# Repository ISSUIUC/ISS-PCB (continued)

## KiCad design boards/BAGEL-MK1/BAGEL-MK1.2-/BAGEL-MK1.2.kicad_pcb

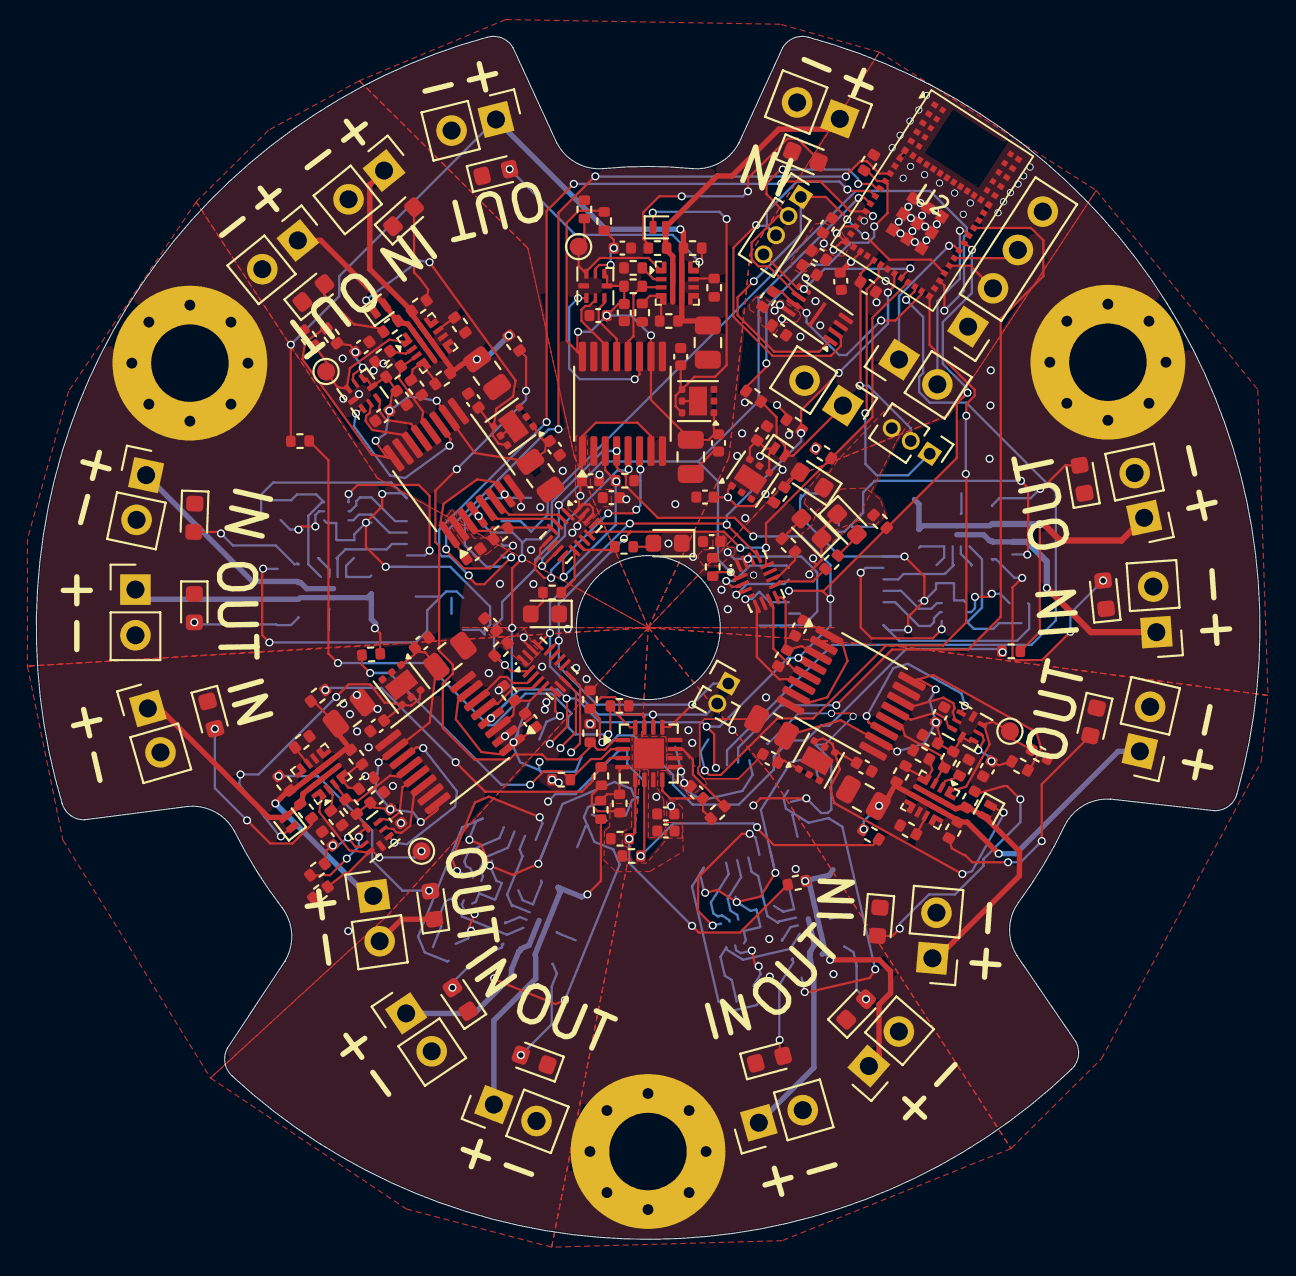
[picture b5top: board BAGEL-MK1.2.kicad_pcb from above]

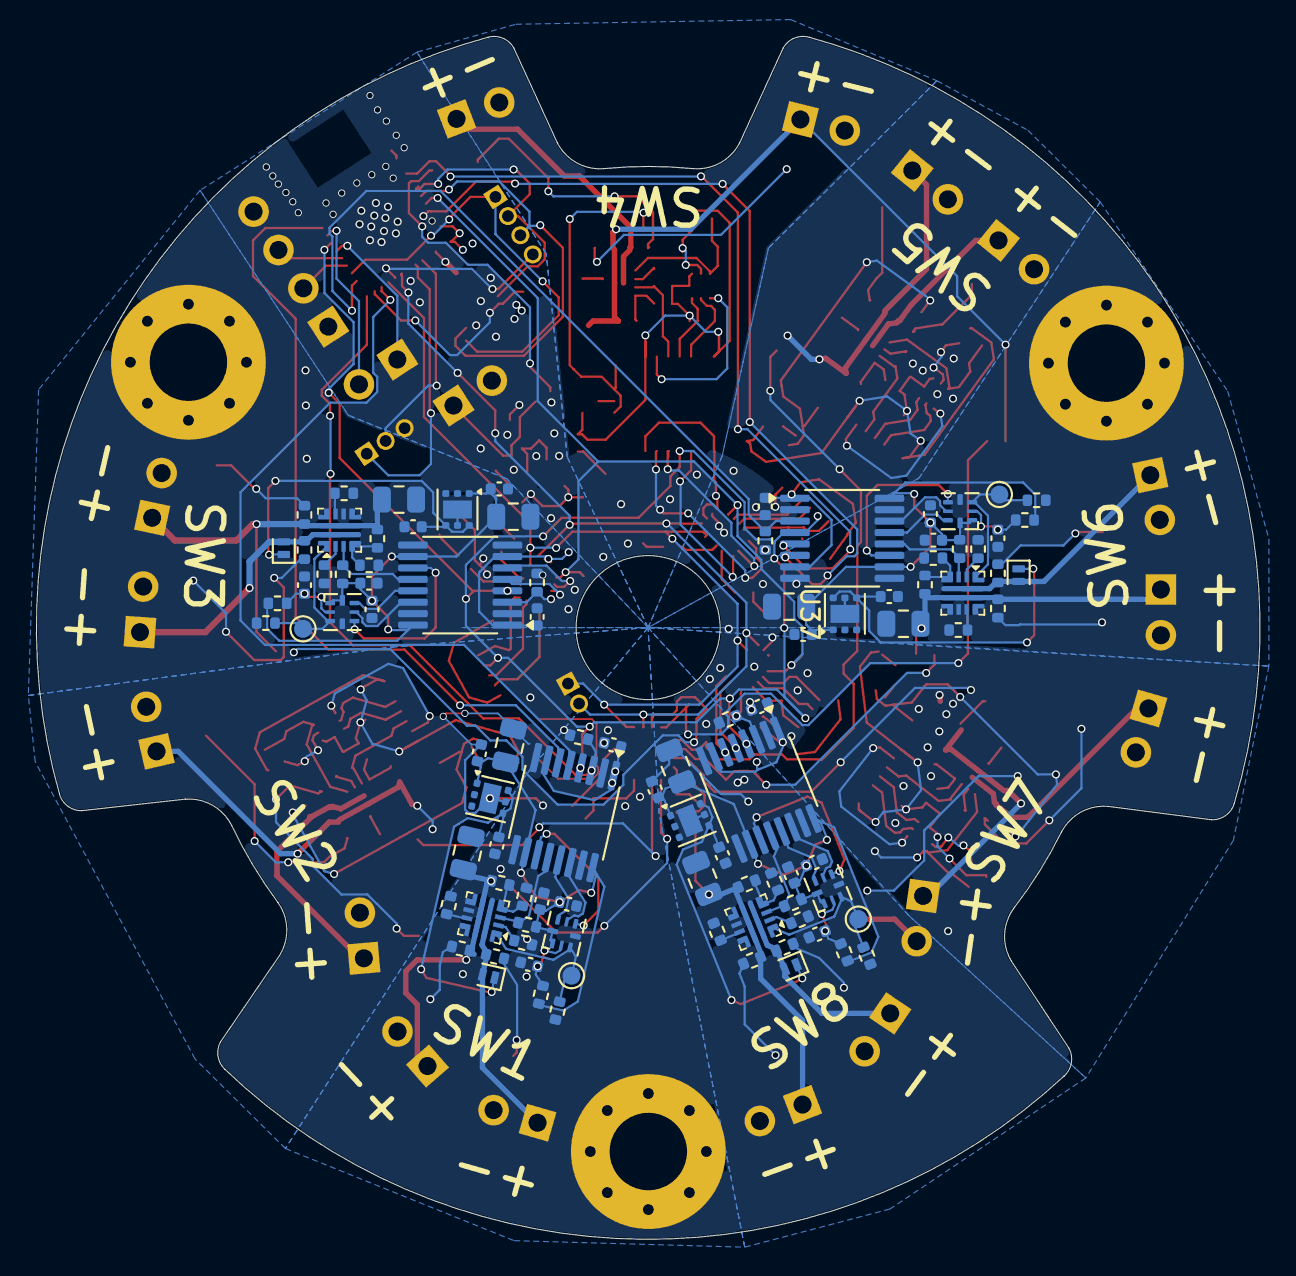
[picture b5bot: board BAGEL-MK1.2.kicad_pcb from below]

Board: 4 copper layers, 68.0 x 66.8 mm, 290 parts (96 on the bottom side), 192 nets.

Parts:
C1, C3, C4, C5, C8, C9, C13, C14, C15, C19, C21, C22, C23, C27, C29, C30, C31, C35, C37, C38, C39, C43, C45, C46, C47, C51, C53, C54, C55, C59, C61, C62, C63, C67, C69, C70, C71, C75, C77: 100nF; C_0402_1005Metric
C2: 4.7uF; C_0402_1005Metric
C6, C10, C11, C12, C16, C24, C32, C40, C48, C56, C64, C72: 1uF; C_0402_1005Metric
C7, C17, C25, C33, C41, C49, C57, C65, C73: 2.2uF; C_0402_1005Metric
C18, C26, C34, C42, C50, C58, C66, C74: 100uF; C_0805_2012Metric
C20, C28, C36, C44, C52, C60, C68, C76: 22uF; C_0805_2012Metric
D1, D7, D10, D13, D16, D19, D22, D25, D28: SDM05U40CSP-7; D_SOD-882
D2, D3, D8, D11, D14, D17, D20, D23, D26, D29: RED; LED_0603_1608Metric
D4: ORANGE; LED_0603_1608Metric
D5, D9, D12, D15, D18, D21, D24, D27, D30: GREEN; LED_0603_1608Metric
D6: BLUE; LED_0603_1608Metric
H1, H2, H3: MountingHole_Pad; MountingHole_4.3mm_M4_Pad_Via
J1: Conn_01x04; PinHeader_1x04_P2.54mm_Vertical
J2: Conn_01x03; PinHeader_1x03_P1.27mm_Vertical
J3: Conn_01x02; PinHeader_1x02_P1.27mm_Vertical
J4, J6, J7, J8, J9, J10, J11, J12, J13, J14, J15, J16, J17, J18, J19, J20, J21, J22: Conn_01x02; PinHeader_1x02_P2.54mm_Vertical
J5: Conn_01x04; PinHeader_1x04_P1.27mm_Vertical
J23, J24, J25, J26, J27, J28, J29, J30: Conn_01x01; TestPoint_Pad_D1.0mm
R1, R2, R3, R12, R15, R16, R18, R19, R25, R26, R28, R29, R35, R36, R38, R39, R45, R46, R48, R49, R55, R56, R58, R59, R65, R66, R68, R69, R75, R76, R78, R79, R85, R86, R88, R89, R95: 10k; R_0402_1005Metric
R4, R6, R7, R8, R9, R10, R11, R17, R27, R37, R47, R57, R67, R77, R87: 4.7k; R_0402_1005Metric
R5, R13, R14, R96, R97, R98, R99, R100, R101, R102, R103, R104, R105, R106, R107, R108, R109, R110, R111: 100k; R_0402_1005Metric
R20, R30, R40, R50, R60, R70, R80, R90: 680; R_0402_1005Metric
R21, R31, R41, R51, R61, R71, R81, R91: 390k; R_0402_1005Metric
R22, R32, R42, R52, R62, R72, R82, R92: 300k; R_0402_1005Metric
R23, R33, R43, R53, R63, R73, R83, R93: 500k; R_0402_1005Metric
R24, R34, R44, R54, R64, R74, R84, R94: 1k; R_0402_1005Metric
U1: W25Q16JLUX; Winbond_USON-8-1EP_3x2mm_P0.5mm_EP0.2x1.6mm
U2: STM32WB1MMC; ST_LGA-77_6.5x10mm_P0.45-0.5mm
U3, U9, U13, U17, U21, U25, U29, U33, U37: TPS7A25; WSON-6-1EP_2x2mm_P0.65mm_EP1x1.6mm
U4, U5, U39: TCAL9538; UQFN-16_1.8x2.6mm_P0.4mm
U6: ADS7138-Q1; WQFN-16-1EP_3x3mm_P0.5mm_EP1.68x1.68mm
U7, U11, U15, U19, U23, U27, U31, U35: ISO7742; SSOP-16_3.9x4.9mm_P0.635mm
U8, U12, U16, U20, U24, U28, U32, U36: SN74AUP1G74RSER; UQFN-RSE0008A
U10, U14, U18, U22, U26, U30, U34, U38: TPS25947; VQFN-HR-RPW0010A

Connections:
/BLUE_LED: R9.1, U5.10 (P7)
/BOOT: J2.2, R2.2, U2.22 (BOOT0)
/EXP_RESET: R3.1, R95.1, U2.13 (PA2), U4.1 (~RESET), U5.1 (~RESET), U39.1 (~RESET)
/FLASH_CS: J5.1, U1.1 (~CS), U2.33 (PB4)
/FLASH_RESET: R1.2, U1.7 (~HOLD/~RESET/IO_{3}), U2.29 (PA7)
/GPIO_Clock: R12.2, U2.37 (PA0), U7.4 (INB), U11.4 (INB), U15.4 (INB), U19.4 (INB), U23.4 (INB), U27.4 (INB), U31.4 (INB), U35.4 (INB)
/GREEN_LED: R8.1, U5.9 (P6)
/I2C_SCL: J3.1, R11.1, U2.27 (PB6), U4.12 (SCL), U5.12 (SCL), U6.13 (SCL), U39.12 (SCL)
/I2C_SDA: J3.2, R10.1, U2.25 (PB7), U4.13 (SDA), U5.13 (SDA), U6.14 (SDA), U39.13 (SDA)
/MainBatt_V: D1.2 (A), J6.1, R13.2
/NRST: J2.1, U2.23 (NRST)
/ORANGE_LED: R7.1, U4.10 (P7)
/PG_ISO_1: U2.28 (PA3), U15.5 (OUTC)
/PG_ISO_2: U4.7 (P4), U19.5 (OUTC)
/PG_ISO_3: U4.3 (P1), U23.5 (OUTC)
/PG_ISO_4: U5.7 (P4), U27.5 (OUTC)
/PG_ISO_5: U5.3 (P1), U31.5 (OUTC)
/PG_ISO_6: U2.9 (PA4), U35.5 (OUTC)
/PG_ISO_7: U7.5 (OUTC), U39.3 (P1)
/PG_ISO_8: U11.5 (OUTC), U39.7 (P4)
/RED_LED: R6.1, U4.9 (P6)
/SPI_MISO: J5.3, U1.2 (DO/IO_{1}), U2.12 (PA6)
/SPI_MOSI: J5.4, U1.5 (DI/IO_{0}), U2.26 (PB5)
/SPI_SCK: J5.2, U1.6 (CLK), U2.11 (PA1)
/SWCLK: J1.2, U2.34 (PA14)
/SWDIO: J1.3, U2.35 (PA13)
/SubBatt_GND1: C29.2, C31.2, C32.2, C33.2, C34.2, C35.1, C36.2, D14.1 (K), D15.1 (K), J7.2, J8.2, R36.1, R40.1, R41.2, R43.2, U15.9 (GND2), U15.15 (GND2), U16.4 (GND), U17.5 (GND), U17.7 (Thermal), U18.8 (GND)
/SubBatt_GND2: C37.2, C39.2, C40.2, C41.2, C42.2, C43.1, C44.2, D17.1 (K), D18.1 (K), J9.2, J10.2, R46.1, R50.1, R51.2, R53.2, U19.9 (GND2), U19.15 (GND2), U20.4 (GND), U21.5 (GND), U21.7 (Thermal), U22.8 (GND)
/SubBatt_GND3: C45.2, C47.2, C48.2, C49.2, C50.2, C51.1, C52.2, D20.1 (K), D21.1 (K), J11.2, J12.2, R56.1, R60.1, R61.2, R63.2, U23.9 (GND2), U23.15 (GND2), U24.4 (GND), U25.5 (GND), U25.7 (Thermal), U26.8 (GND)
/SubBatt_GND4: C53.2, C55.2, C56.2, C57.2, C58.2, C59.1, C60.2, D23.1 (K), D24.1 (K), J13.2, J14.2, R66.1, R70.1, R71.2, R73.2, U27.9 (GND2), U27.15 (GND2), U28.4 (GND), U29.5 (GND), U29.7 (Thermal), U30.8 (GND)
/SubBatt_GND5: C61.2, C63.2, C64.2, C65.2, C66.2, C67.1, C68.2, D26.1 (K), D27.1 (K), J15.2, J16.2, R76.1, R80.1, R81.2, R83.2, U31.9 (GND2), U31.15 (GND2), U32.4 (GND), U33.5 (GND), U33.7 (Thermal), U34.8 (GND)
/SubBatt_GND6: C69.2, C71.2, C72.2, C73.2, C74.2, C75.1, C76.2, D29.1 (K), D30.1 (K), J17.2, J18.2, R86.1, R90.1, R91.2, R93.2, U35.9 (GND2), U35.15 (GND2), U36.4 (GND), U37.5 (GND), U37.7 (Thermal), U38.8 (GND)
/SubBatt_GND7: C13.2, C15.2, C16.2, C17.2, C18.2, C19.1, C20.2, D8.1 (K), D9.1 (K), J19.2, J20.2, R16.1, R20.1, R21.2, R23.2, U7.9 (GND2), U7.15 (GND2), U8.4 (GND), U9.5 (GND), U9.7 (Thermal), U10.8 (GND)
/SubBatt_GND8: C21.2, C23.2, C24.2, C25.2, C26.2, C27.1, C28.2, D11.1 (K), D12.1 (K), J21.2, J22.2, R26.1, R30.1, R31.2, R33.2, U11.9 (GND2), U11.15 (GND2), U12.4 (GND), U13.5 (GND), U13.7 (Thermal), U14.8 (GND)
/SubBatt_V1: D13.2 (A), J7.1, R37.1, U18.5 (IN)
/SubBatt_V2: D16.2 (A), J9.1, R47.1, U22.5 (IN)
/SubBatt_V3: D19.2 (A), J11.1, R57.1, U26.5 (IN)
/SubBatt_V4: D22.2 (A), J13.1, R67.1, U30.5 (IN)
/SubBatt_V5: D25.2 (A), J15.1, R77.1, U34.5 (IN)
/SubBatt_V6: D28.2 (A), J17.1, R87.1, U38.5 (IN)
/SubBatt_V7: D7.2 (A), J19.1, R17.1, U10.5 (IN)
/SubBatt_V8: D10.2 (A), J21.1, R27.1, U14.5 (IN)
/Switch 1/PG: R39.2, U15.12 (INC), U18.3 (PG/AUXOFF)
/Switch 1/Q: J25.1 (Pin_1_1), R36.2, U16.3 (Q), U18.1 (EN/UVLO)
/Switch 1/Reg_V: C29.1, C31.1, C33.1, C34.1, R38.1, R39.1, U15.10 (EN2), U15.16 (VCC2), U16.1 (~PRE), U16.8 (VCC), U17.1 (VOUT)
/Switch 1/~CLR: C35.2, R38.2, U16.2 (~CLR)
/Switch 1/~Q: U15.11 (IND), U16.5 (~Q)
/Switch 2/PG: R49.2, U19.12 (INC), U22.3 (PG/AUXOFF)
/Switch 2/Q: J26.1 (Pin_1_1), R46.2, U20.3 (Q), U22.1 (EN/UVLO)
/Switch 2/Reg_V: C37.1, C39.1, C41.1, C42.1, R48.1, R49.1, U19.10 (EN2), U19.16 (VCC2), U20.1 (~PRE), U20.8 (VCC), U21.1 (VOUT)
/Switch 2/~CLR: C43.2, R48.2, U20.2 (~CLR)
/Switch 2/~Q: U19.11 (IND), U20.5 (~Q)
/Switch 3/PG: R59.2, U23.12 (INC), U26.3 (PG/AUXOFF)
/Switch 3/Q: J27.1 (Pin_1_1), R56.2, U24.3 (Q), U26.1 (EN/UVLO)
/Switch 3/Reg_V: C45.1, C47.1, C49.1, C50.1, R58.1, R59.1, U23.10 (EN2), U23.16 (VCC2), U24.1 (~PRE), U24.8 (VCC), U25.1 (VOUT)
/Switch 3/~CLR: C51.2, R58.2, U24.2 (~CLR)
/Switch 3/~Q: U23.11 (IND), U24.5 (~Q)
/Switch 4/PG: R69.2, U27.12 (INC), U30.3 (PG/AUXOFF)
/Switch 4/Q: J28.1 (Pin_1_1), R66.2, U28.3 (Q), U30.1 (EN/UVLO)
/Switch 4/Reg_V: C53.1, C55.1, C57.1, C58.1, R68.1, R69.1, U27.10 (EN2), U27.16 (VCC2), U28.1 (~PRE), U28.8 (VCC), U29.1 (VOUT)
/Switch 4/~CLR: C59.2, R68.2, U28.2 (~CLR)
/Switch 4/~Q: U27.11 (IND), U28.5 (~Q)
/Switch 5/PG: R79.2, U31.12 (INC), U34.3 (PG/AUXOFF)
/Switch 5/Q: J29.1 (Pin_1_1), R76.2, U32.3 (Q), U34.1 (EN/UVLO)
/Switch 5/Reg_V: C61.1, C63.1, C65.1, C66.1, R78.1, R79.1, U31.10 (EN2), U31.16 (VCC2), U32.1 (~PRE), U32.8 (VCC), U33.1 (VOUT)
/Switch 5/~CLR: C67.2, R78.2, U32.2 (~CLR)
/Switch 5/~Q: U31.11 (IND), U32.5 (~Q)
/Switch 6/PG: R89.2, U35.12 (INC), U38.3 (PG/AUXOFF)
/Switch 6/Q: J30.1 (Pin_1_1), R86.2, U36.3 (Q), U38.1 (EN/UVLO)
/Switch 6/Reg_V: C69.1, C71.1, C73.1, C74.1, R88.1, R89.1, U35.10 (EN2), U35.16 (VCC2), U36.1 (~PRE), U36.8 (VCC), U37.1 (VOUT)
/Switch 6/~CLR: C75.2, R88.2, U36.2 (~CLR)
/Switch 6/~Q: U35.11 (IND), U36.5 (~Q)
/Switch 7/PG: R19.2, U7.12 (INC), U10.3 (PG/AUXOFF)
/Switch 7/Q: J23.1 (Pin_1_1), R16.2, U8.3 (Q), U10.1 (EN/UVLO)
/Switch 7/Reg_V: C13.1, C15.1, C17.1, C18.1, R18.1, R19.1, U7.10 (EN2), U7.16 (VCC2), U8.1 (~PRE), U8.8 (VCC), U9.1 (VOUT)
/Switch 7/~CLR: C19.2, R18.2, U8.2 (~CLR)
/Switch 7/~Q: U7.11 (IND), U8.5 (~Q)
/Switch 8/PG: R29.2, U11.12 (INC), U14.3 (PG/AUXOFF)
/Switch 8/Q: J24.1 (Pin_1_1), R26.2, U12.3 (Q), U14.1 (EN/UVLO)
/Switch 8/Reg_V: C21.1, C23.1, C25.1, C26.1, R28.1, R29.1, U11.10 (EN2), U11.16 (VCC2), U12.1 (~PRE), U12.8 (VCC), U13.1 (VOUT)
/Switch 8/~CLR: C27.2, R28.2, U12.2 (~CLR)
/Switch 8/~Q: U11.11 (IND), U12.5 (~Q)
/Switch_1: R35.1, U2.30 (PA12), U15.3 (INA)
/Switch_2: R45.1, U4.8 (P5), U19.3 (INA)
/Switch_3: R55.1, U4.4 (P2), U23.3 (INA)
/Switch_4: R65.1, U5.8 (P5), U27.3 (INA)
/Switch_5: R75.1, U5.4 (P2), U31.3 (INA)
/Switch_6: R85.1, U2.32 (PA11), U35.3 (INA)
/Switch_7: R15.1, U7.3 (INA), U39.4 (P2)
/Switch_8: R25.1, U11.3 (INA), U39.5 (P3)
/UART_RX: J4.1, U2.36 (PA10)
/UART_TX: J4.2, U2.38 (PA9)
/VOUT_SENSE_1: R96.1, R97.2, U6.5 (AIN6/GPIO6)
/VOUT_SENSE_2: R98.1, R99.2, U6.6 (AIN7/GPIO7)
/VOUT_SENSE_3: R100.1, R101.2, U6.15 (AIN0/GPIO0)
/VOUT_SENSE_4: R102.1, R103.2, U6.16 (AIN1/GPIO1)
/VOUT_SENSE_5: R104.1, R105.2, U6.1 (ANI2/GPIO2)
/VOUT_SENSE_6: R106.1, R107.2, U6.2 (AIN3/GPIO3)
/VOUT_SENSE_7: R108.1, R109.2, U6.3 (AIN4/GPIO4)
/VOUT_SENSE_8: R110.1, R111.2, U6.4 (AIN5/GPIO5)
/V_SENSE: R13.1, R14.2, U2.10 (PA8)
/V_out_1: C36.1, J8.1, R42.1, R44.1, R96.2, U18.6 (OUT)
/V_out_2: C44.1, J10.1, R52.1, R54.1, R98.2, U22.6 (OUT)
/V_out_3: C52.1, J12.1, R62.1, R64.1, R100.2, U26.6 (OUT)
/V_out_4: C60.1, J14.1, R72.1, R74.1, R102.2, U30.6 (OUT)
/V_out_5: C68.1, J16.1, R82.1, R84.1, R104.2, U34.6 (OUT)
/V_out_6: C76.1, J18.1, R92.1, R94.1, R106.2, U38.6 (OUT)
/V_out_7: C20.1, J20.1, R22.1, R24.1, R108.2, U10.6 (OUT)
/V_out_8: C28.1, J22.1, R32.1, R34.1, R110.2, U14.6 (OUT)
/~Q_ISO_1: U2.39 (PA5), U15.6 (OUTD)
/~Q_ISO_2: U4.5 (P3), U19.6 (OUTD)
/~Q_ISO_3: U4.2 (P0), U23.6 (OUTD)
/~Q_ISO_4: U5.5 (P3), U27.6 (OUTD)
/~Q_ISO_5: U5.2 (P0), U31.6 (OUTD)
/~Q_ISO_6: U2.14 (PB8), U35.6 (OUTD)
/~Q_ISO_7: U7.6 (OUTD), U39.2 (P0)
/~Q_ISO_8: U11.6 (OUTD), U39.8 (P5)
MCU_GND: C1.2, C2.2, C3.2, C4.2, C5.2, C6.2, C7.2, C8.2, C9.2, C11.2, C12.2, C14.2, C22.2, C30.2, C38.2, C46.2, C54.2, C62.2, C70.2, C77.2, D2.1 (K), D3.1 (K), D4.1 (K), D5.1 (K), D6.1 (K), J1.4, J2.3, J6.2, R2.1, R12.1, R14.1, R15.2, R25.2, R35.2, R45.2, R55.2, R65.2, R75.2, R85.2, R97.1, R99.1, R101.1, R103.1, R105.1, R107.1, R109.1, R111.1, U1.4 (GND), U1.9 (EP), U2.1 (VSS), U2.2 (VSS), U2.3 (VSS), U2.4 (VSS), U2.5 (VSSRF), U2.8 (VSSRF), U2.15 (VSS), U2.17 (VSS), U2.19 (VSS), U2.21 (VSSSMPS), U2.24 (VSS), U2.31 (VSS), U2.43 (VSS), U2.44 (VSS), U2.45 (VSS), U2.46 (VSS), U2.47 (VSS), U2.48 (VSS), U2.49 (VSS), U2.50 (VSS), U2.51 (VSS), U2.52 (VSS), U2.53 (VSS), U2.54 (VSS), U2.55 (VSS), U2.56 (VSS), U2.57 (VSS), U2.58 (VSS), U2.59 (VSS), U2.60 (VSS), U2.61 (VSS), U2.62 (VSS), U2.63 (VSS), U2.64 (VSS), U2.65 (VSS), U2.66 (VSS), U2.67 (VSS), U2.68 (VSS), U2.69 (VSS), U2.70 (VSS), U2.71 (VSS), U2.72 (VSS), U2.73 (VSS), U2.74 (VSS), U2.75 (VSS), U2.76 (VSS), U2.77 (VSS), U3.5 (GND), U3.7 (Thermal), U4.6 (GND), U4.16 (A1), U5.6 (GND), U5.15 (A0), U7.2 (GND1), U7.8 (GND1), U11.2 (GND1), U11.8 (GND1), U15.2 (GND1), U15.8 (GND1), U19.2 (GND1), U19.8 (GND1), U23.2 (GND1), U23.8 (GND1), U27.2 (GND1), U27.8 (GND1), U31.2 (GND1), U31.8 (GND1), U35.2 (GND1), U35.8 (GND1), U39.6 (GND)
MCU_V: C1.1, C2.1, C3.1, C4.1, C5.1, C7.1, C8.1, C9.1, C10.2, C11.1, C12.1, C14.1, C22.1, C30.1, C38.1, C46.1, C54.1, C62.1, C70.1, C77.1, J1.1, R1.1, R3.2, R4.2, R10.2, R11.2, R95.2, U1.8 (VCC), U2.16 (VDDA), U2.18 (VBAT), U2.20 (VDDSMPS), U3.1 (VOUT), U4.14 (VCC), U4.15 (A0), U5.14 (VCC), U5.16 (A1), U6.7 (AVDD), U6.9 (GND), U6.10 (DVDD), U6.17 (EPAD), U7.1 (VCC1), U7.7 (EN1), U11.1 (VCC1), U11.7 (EN1), U15.1 (VCC1), U15.7 (EN1), U19.1 (VCC1), U19.7 (EN1), U23.1 (VCC1), U23.7 (EN1), U27.1 (VCC1), U27.7 (EN1), U31.1 (VCC1), U31.7 (EN1), U35.1 (VCC1), U35.7 (EN1), U39.14 (VCC), U39.15 (A0), U39.16 (A1)
unnamed: C6.1, D1.1 (K), U3.4 (EN), U3.6 (VIN)
unnamed: D2.2 (A), R4.1
unnamed: D3.2 (A), R6.2
unnamed: D4.2 (A), R7.2
unnamed: D5.2 (A), R8.2
unnamed: D6.2 (A), R9.2
unnamed: C16.1, D7.1 (K), U9.4 (EN), U9.6 (VIN)
unnamed: D8.2 (A), R17.2
unnamed: D9.2 (A), R24.2
unnamed: C24.1, D10.1 (K), U13.4 (EN), U13.6 (VIN)
unnamed: D11.2 (A), R27.2
unnamed: D12.2 (A), R34.2
unnamed: C32.1, D13.1 (K), U17.4 (EN), U17.6 (VIN)
unnamed: D14.2 (A), R37.2
unnamed: D15.2 (A), R44.2
unnamed: C40.1, D16.1 (K), U21.4 (EN), U21.6 (VIN)
unnamed: D17.2 (A), R47.2
unnamed: D18.2 (A), R54.2
unnamed: C48.1, D19.1 (K), U25.4 (EN), U25.6 (VIN)
unnamed: D20.2 (A), R57.2
unnamed: D21.2 (A), R64.2
unnamed: C56.1, D22.1 (K), U29.4 (EN), U29.6 (VIN)
unnamed: D23.2 (A), R67.2
unnamed: D24.2 (A), R74.2
unnamed: C64.1, D25.1 (K), U33.4 (EN), U33.6 (VIN)
unnamed: D26.2 (A), R77.2
unnamed: D27.2 (A), R84.2
unnamed: C72.1, D28.1 (K), U37.4 (EN), U37.6 (VIN)
unnamed: D29.2 (A), R87.2
unnamed: D30.2 (A), R94.2
unnamed: U2.6 (ANT_IN), U2.7 (ANT_OUT)
unnamed: R5.1, U6.11 (ADDR)
unnamed: C10.1, R5.2, U6.8 (DECAP)
unnamed: U7.14 (OUTA), U8.6 (D)
unnamed: U7.13 (OUTB), U8.7 (CLK)
unnamed: R20.2, U10.9 (ILM)
unnamed: R21.1, U10.2 (OVLO/OVCSEL)
unnamed: R22.2, R23.1, U10.4 (PGTH/NFLT)
unnamed: U11.14 (OUTA), U12.6 (D)
unnamed: U11.13 (OUTB), U12.7 (CLK)
unnamed: R30.2, U14.9 (ILM)
unnamed: R31.1, U14.2 (OVLO/OVCSEL)
unnamed: R32.2, R33.1, U14.4 (PGTH/NFLT)
unnamed: U15.14 (OUTA), U16.6 (D)
unnamed: U15.13 (OUTB), U16.7 (CLK)
unnamed: R40.2, U18.9 (ILM)
unnamed: R41.1, U18.2 (OVLO/OVCSEL)
unnamed: R42.2, R43.1, U18.4 (PGTH/NFLT)
unnamed: U19.14 (OUTA), U20.6 (D)
unnamed: U19.13 (OUTB), U20.7 (CLK)
unnamed: R50.2, U22.9 (ILM)
unnamed: R51.1, U22.2 (OVLO/OVCSEL)
unnamed: R52.2, R53.1, U22.4 (PGTH/NFLT)
unnamed: U23.14 (OUTA), U24.6 (D)
unnamed: U23.13 (OUTB), U24.7 (CLK)
unnamed: R60.2, U26.9 (ILM)
unnamed: R61.1, U26.2 (OVLO/OVCSEL)
unnamed: R62.2, R63.1, U26.4 (PGTH/NFLT)
unnamed: U27.14 (OUTA), U28.6 (D)
unnamed: U27.13 (OUTB), U28.7 (CLK)
unnamed: R70.2, U30.9 (ILM)
unnamed: R71.1, U30.2 (OVLO/OVCSEL)
unnamed: R72.2, R73.1, U30.4 (PGTH/NFLT)
unnamed: U31.14 (OUTA), U32.6 (D)
unnamed: U31.13 (OUTB), U32.7 (CLK)
unnamed: R80.2, U34.9 (ILM)
unnamed: R81.1, U34.2 (OVLO/OVCSEL)
unnamed: R82.2, R83.1, U34.4 (PGTH/NFLT)
unnamed: U35.14 (OUTA), U36.6 (D)
unnamed: U35.13 (OUTB), U36.7 (CLK)
unnamed: R90.2, U38.9 (ILM)
unnamed: R91.1, U38.2 (OVLO/OVCSEL)
unnamed: R92.2, R93.1, U38.4 (PGTH/NFLT)

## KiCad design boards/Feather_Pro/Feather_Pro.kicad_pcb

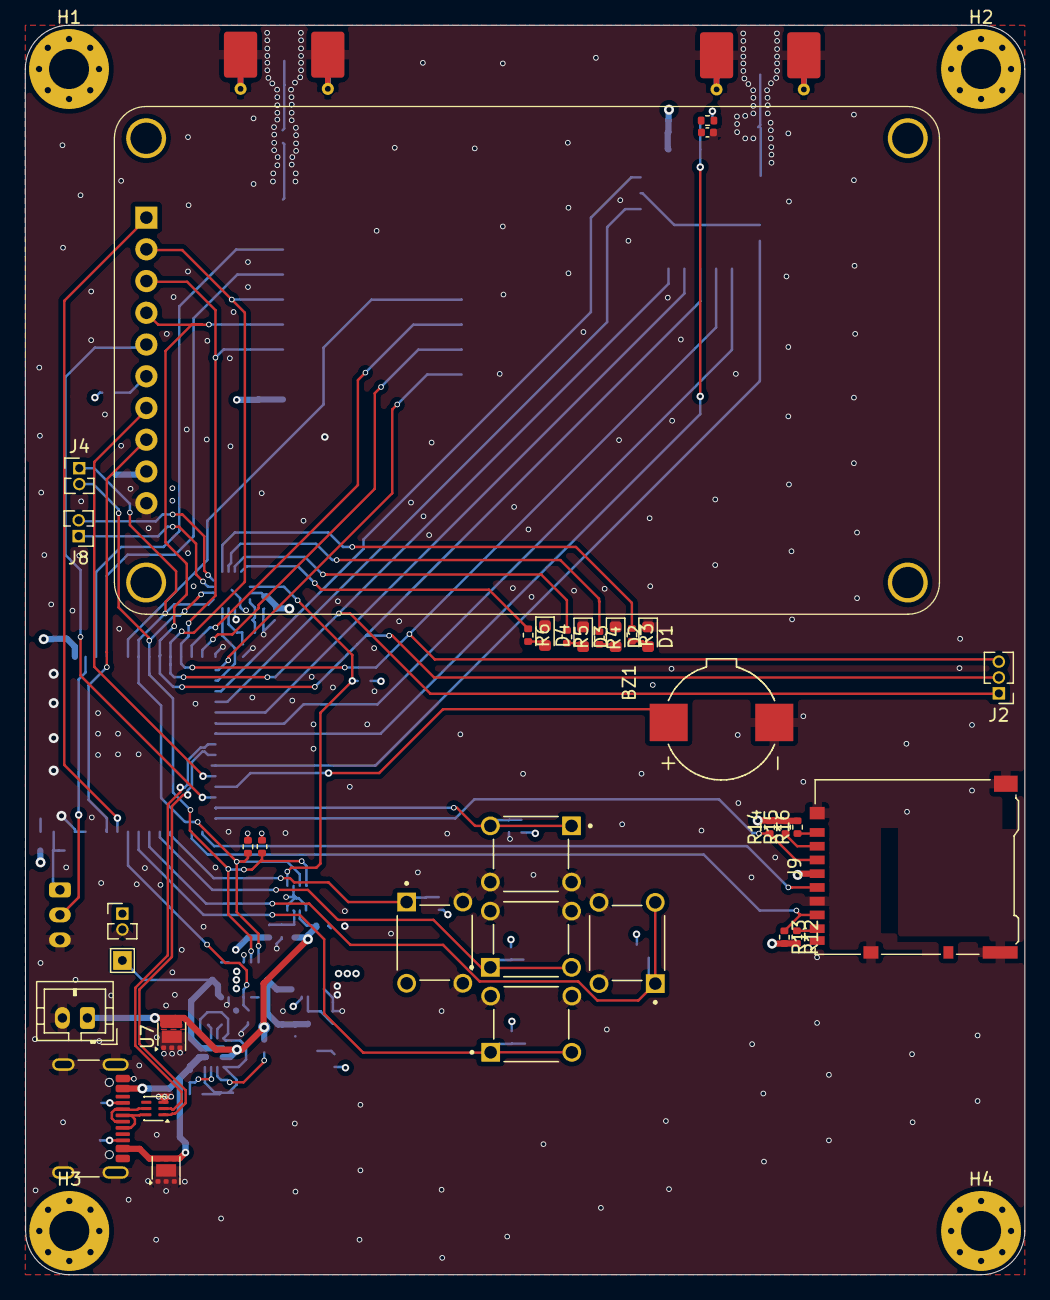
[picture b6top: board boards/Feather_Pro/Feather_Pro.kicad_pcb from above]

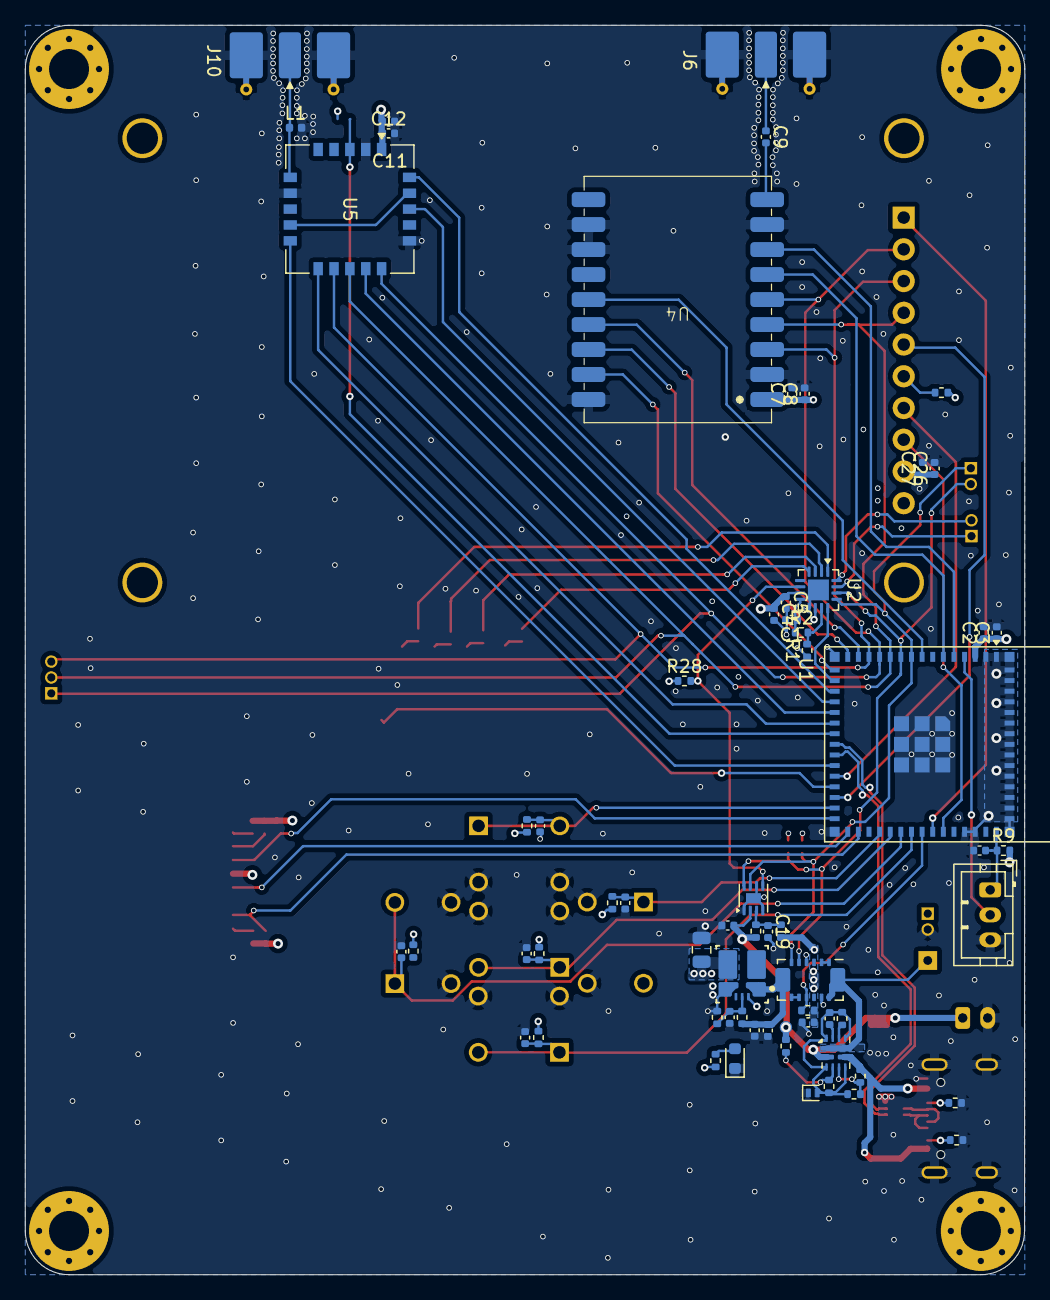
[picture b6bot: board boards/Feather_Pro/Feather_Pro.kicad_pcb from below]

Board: 4 copper layers, 80.0 x 100.0 mm, 102 parts (63 on the bottom side), 77 nets.

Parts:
BZ1: Buzzer; Buzzer_SMTB-0927-TW-R
C1, C4, C5, C6, C7, C17, C19, C26: 1uF; C_0402_1005Metric
C2: 22uF; C_0402_1005Metric
C3, C8, C10, C14, C18, C20, C21, C22, C23, C24, C25, C27: 100nF; C_0402_1005Metric
C9: 100pF; C_0402_1005Metric
C11: 10uF; C_0402_1005Metric
C12, C15: 10nF; C_0402_1005Metric
C13: 10uf; C_0402_1005Metric
C16: 22uF; C_0805_2012Metric
D1: RED LED; LED_0603_1608Metric
D2: ORANGE LED; LED_0603_1608Metric
D3: GREEN LED; LED_0603_1608Metric
D4: BLUE LED; LED_0603_1608Metric
D5: BAS116L; D_SOD-882
D6: LED; LED_0603_1608Metric
H1, H2, H3, H4: M3; MountingHole_3.2mm_M3_Pad_Via
J1: USB4105-GF-A; USB_C_Receptacle_GCT_USB4105-xx-A_16P_TopMnt_Horizontal
J2: Conn_01x03; PinHeader_1x03_P1.27mm_Vertical
J3: Conn_01x03; JST_PH_B3B-PH-K_1x03_P2.00mm_Vertical
J4, J5, J8: Conn_01x02; PinHeader_1x02_P1.27mm_Vertical
J6, J10: SMA; SMA_Molex_73251-2120_EdgeMount_Horizontal
J7: Conn_01x02; JST_PH_B2B-PH-K_1x02_P2.00mm_Vertical
J9: DM3AT-SF-PEJM5; microSD_HC_Hirose_DM3AT-SF-PEJM5
J11: TestPoint; TestPoint_THTPad_1.5x1.5mm_Drill0.7mm
L1: 330nH; L_0402_1005Metric
R1, R26, R27: 0; R_0402_1005Metric
R2, R17, R35: 100k; R_0402_1005Metric
R3, R4, R5, R6, R25: 470; R_0402_1005Metric
R7, R8: 4.7k; R_0402_1005Metric
R9: 20k; R_0402_1005Metric
R10, R11: 5.1k; R_0402_1005Metric
R12, R13, R14, R15, R16, R19, R29, R30, R31, R32, R33, R34: 10k; R_0402_1005Metric
R18: 11.8k; R_0402_1005Metric
R20, R22: 16.9k; R_0402_1005Metric
R21, R23: 5k; R_0402_1005Metric
R24: 21.5k; R_0402_1005Metric
R28: 10K; R_0402_1005Metric
SW1, SW2, SW3, SW4, SW5: SW_Push; SW_TL1105AF160Q
U1: ESP32-S3-MINI-1; ESP32-S2-MINI-1
U2: ADS7138-Q1; WQFN-16-1EP_3x3mm_P0.5mm_EP1.68x1.68mm
U3: ECMF02-2AMX6; ST_UQFN-6L_1.5x1.7mm_P0.5mm
U4: LR2021
U5: E22-400MM22S
U6, U7: TVS1800DRV; WSON-6-1EP_2x2mm_P0.65mm_EP1x1.6mm
U8: TPSM863253RDXR; QFN-FCMOD-RDX0007A
U9: TPS2121; Texas_VQFN-HR-12_2x2.5mm_P0.5mm
U10: MAX17048G+T10; TDFN-8-1EP_2x2mm_P0.5mm_EP0.8x1.2mm
U11: INA745x; VQFN-REL0014B
U12: LCD_2.2_in; Adafruit_2.2_LCD_SCREEN

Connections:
+3V3: C2.1, C3.1, C4.1, C5.1, C7.1, C8.1, C11.1, C12.1, C16.1, C20.2, C26.1, C27.1, J5.1, J9.4 (VDD), R7.2, R8.2, R9.2, R12.2, R13.2, R14.2, R15.2, R16.2, R17.2, R25.1, R27.1, R28.1, R29.1, R30.2, R31.2, R32.2, R33.2, R34.2, R35.1, U1.3 (3V3), U2.7 (AVDD), U2.10 (DVDD), U4.1 (VCC), U5.1 (VCC), U8.3 (VOUT), U8.7 (FB), U11.3 (A1), U11.11 (VS), U12.9 (VIN)
/ADS_ALERT: U1.17 (IO13), U2.12 (ALERT)
/BOOT_SW: J3.2, U1.4 (IO0)
/BUTTON_CENTER: C25.1, R34.1, SW5.1, SW5.2, U1.35 (IO39)
/BUTTON_DOWN: C22.1, R31.1, SW2.1, SW2.2, U1.37 (IO41)
/BUTTON_LEFT: C24.1, R33.1, SW4.1, U1.34 (IO38)
/BUTTON_RIGHT: C21.1, R30.1, SW1.1, SW1.2, U1.36 (IO40)
/BUTTON_UP: C23.1, R32.1, SW3.1, SW3.2, U1.29 (IO34)
/BUZZER: BZ1.1 (+), U1.27 (IO47)
/D+: J1.A6 (D+), J1.B6 (D+), U3.6 (D+_out)
/D-: J1.A7 (D-), J1.B7 (D-), U3.5 (D-_out)
/E22_BUSY: U1.21 (IO17), U5.11 (BUSY)
/E22_CS: U1.20 (IO16), U5.14 (NSS)
/E22_DIO1: U1.18 (IO14), U5.20 (DIO1)
/E22_DIO3: U1.19 (IO15), U5.18 (DIO3)
/E22_RESET: C10.1, R17.1, U1.22 (IO18), U5.3 (NRST)
/E22_RXEN: U1.25 (IO21), U5.10 (RXEN)
/Feather_Pro_Power/PMUX_GND: C17.1, D5.2 (A), R21.2, R23.2, R24.1, U9.3 (CP2), U9.6 (PR1), U9.9 (ST), U9.12 (GND)
/GPIO_0: J8.1, U2.15 (AIN0/GPIO0)
/GPIO_1: J8.2, U2.16 (AIN1/GPIO1)
/I2C_SCL: J4.1, R8.1, U1.9 (IO5), U2.13 (SCL), U10.7 (SCL), U11.6 (SCL)
/I2C_SDA: J4.2, R7.1, U1.10 (IO6), U2.14 (SDA), U10.8 (SDA), U11.5 (SDA)
/INA_ALERT: R29.2, U1.38 (IO42), U11.10 (ALERT)
/LCD_BL: U1.39 (TXD0), U12.1 (BL)
/LCD_CS: U1.28 (IO33), U12.5 (CS)
/LCD_D_C: U1.40 (RXD0), U12.8 (D/C)
/LCD_RST: U1.26 (IO26), U12.7 (RST)
/LED_BLUE: R6.1, U2.4 (AIN5/GPIO5)
/LED_GREEN: R5.1, U2.3 (AIN4/GPIO4)
/LED_ORANGE: R4.1, U2.2 (AIN3/GPIO3)
/LED_RED: R3.1, U2.1 (ANI2/GPIO2)
/LR2021_ANT: C9.2, U4.9 (ANT)
/LR2021_BUSY: U1.5 (IO1), U4.7 (BUSY)
/LR2021_CS: U1.6 (IO2), U4.6 (~CS)
/LR2021_GPIO7: U1.16 (IO12), U4.17 (DIO7)
/LR2021_GPIO8: U1.15 (IO11), U4.16 (DIO8)
/LR2021_GPIO9: U1.14 (IO10), U4.15 (DIO9)
/LR2021_nRST: U1.8 (IO4), U4.14 (nRST)
/MAX_ALERT: R28.2, U2.6 (AIN7/GPIO7), U10.5 (*ALRT)
/RESET_SW: C6.1, J3.1, R9.1, U1.45 (EN)
/SD_CLK: J9.5 (CLK), U1.31 (IO35)
/SD_CMD: J9.3 (CMD), R14.1, U1.30 (IO48)
/SD_DAT0: J9.7 (DAT0), R13.1, U1.32 (IO36)
/SPI_MISO: J2.3, U1.13 (IO9), U4.3 (MISO), U5.12 (MISO), U12.3 (MISO)
/SPI_MOSI: J2.2, U1.11 (IO7), U4.4 (MOSI), U5.13 (MOSI), U12.4 (MOSI)
/SPI_SCK: J2.1, U1.12 (IO8), U4.5 (SCK), U5.15 (SCK), U12.2 (SCK)
/SYS_POWER: J11.1 (Pin_1_1), U9.1 (OUT), U9.8 (OUT), U11.13 (VBUS), U11.14 (IS+)
/USB_D+: U1.24 (USB_D+), U3.1 (D+_in)
/USB_D-: U1.23 (USB_D-), U3.2 (D-_in)
/USB_POWER: J1.A4 (VBUS), J1.A9 (VBUS), J1.B4 (VBUS), J1.B9 (VBUS), R20.1, U6.4 (IN), U6.5 (IN), U6.6 (IN), U9.7 (IN1)
/VBAT: C18.1, J7.1, R22.1, R26.1, U7.4 (IN), U7.5 (IN), U7.6 (IN), U9.2 (IN2), U10.2 (CELL)
/VREG_IN: C13.1, C14.1, R18.1, U8.1 (VIN), U11.7 (IS-)
GND: BZ1.2 (-), C1.2, C2.2, C3.2, C4.2, C5.2, C6.2, C7.2, C8.2, C10.2, C11.2, C12.2, C13.2, C14.2, C15.2, C16.2, C18.2, C19.2, C20.1, C21.2, C22.2, C23.2, C24.2, C25.2, C26.2, C27.2, D1.1 (K), D2.1 (K), D3.1 (K), D4.1 (K), D5.1 (K), D6.1 (K), J1.A1 (GND), J1.A12 (GND), J1.B1 (GND), J1.B12 (GND), J1.S1 (SHIELD), J3.3, J5.2, J6.2 (Ext), J7.2, J9.6 (VSS), J9.11 (SHIELD), J10.2 (Ext), L1.2, R1.1, R10.2, R11.2, R19.2, SW1.3, SW1.4, SW2.3, SW2.4, SW3.3, SW3.4, SW4.3, SW4.4, SW5.3, SW5.4, U1.1 (GND), U1.2 (GND), U1.42 (GND), U1.43 (GND), U1.46 (GND), U1.47 (GND), U1.48 (GND), U1.49 (GND), U1.50 (GND), U1.51 (GND), U1.52 (GND), U1.53 (GND), U1.54 (GND), U1.55 (GND), U1.56 (GND), U1.57 (GND), U1.58 (GND), U1.59 (GND), U1.60 (GND), U1.61 (GND), U1.62 (GND), U1.63 (GND), U1.64 (GND), U1.65 (GND), U2.9 (GND), U2.17 (EPAD), U3.3 (GND), U4.2 (GND), U4.8 (GND), U4.11 (GND), U4.12 (GND), U4.18 (GND), U5.2 (GND), U5.7 (GND), U5.16 (GND), U6.1 (GND), U6.2 (GND), U6.3 (GND), U6.7 (GND), U7.1 (GND), U7.2 (GND), U7.3 (GND), U7.7 (GND), U8.4 (PGND), U10.1 (CTG), U10.4 (GND), U10.6 (QSTRT), U10.9 (EPAD), U11.4 (A0), U11.12 (GND), U12.10 (GND)
unnamed: D1.2 (A), R3.2
unnamed: D2.2 (A), R4.2
unnamed: D3.2 (A), R5.2
unnamed: D4.2 (A), R6.2
unnamed: D6.2 (A), R25.2
unnamed: J1.A5 (CC1), R10.1
unnamed: J1.B5 (CC2), R11.1
unnamed: C9.1, J6.1 (In)
unnamed: J9.8 (DAT1), R12.1
unnamed: J9.1 (DAT2), R16.1
unnamed: J9.2 (DAT3/CD), R15.1
unnamed: J10.1 (In), L1.1, U5.6 (ANT)
unnamed: R1.2, R2.2, U2.11 (ADDR)
unnamed: C1.1, R2.1, U2.8 (DECAP)
unnamed: U5.9 (TXEN), U5.19 (DIO2)
unnamed: C15.1, R18.2, R19.1, U8.6 (EN)
unnamed: R24.2, U9.10 (ILM)
unnamed: R20.2, R21.1, U9.5 (OV1)
unnamed: R22.2, R23.1, U9.4 (OV2)
unnamed: C17.2, U9.11 (SS)
unnamed: C19.1, R26.2, R27.2, U10.3 (VDD)
unnamed: U11.1 (SH+), U11.2 (IN+)
unnamed: U11.8 (SH-), U11.9 (IN-)
unnamed: R35.2, U12.6 (SDCS)
